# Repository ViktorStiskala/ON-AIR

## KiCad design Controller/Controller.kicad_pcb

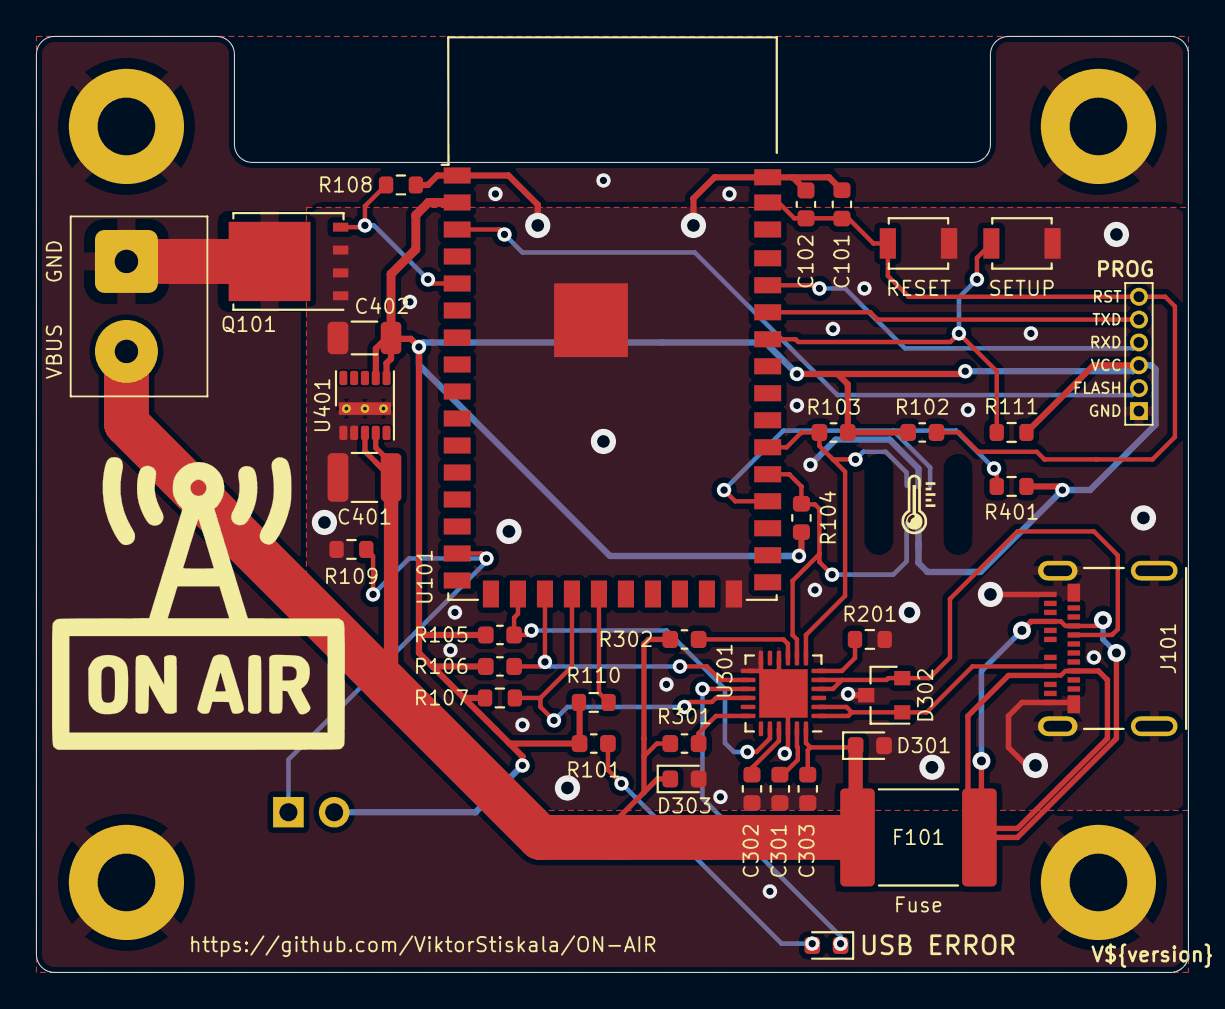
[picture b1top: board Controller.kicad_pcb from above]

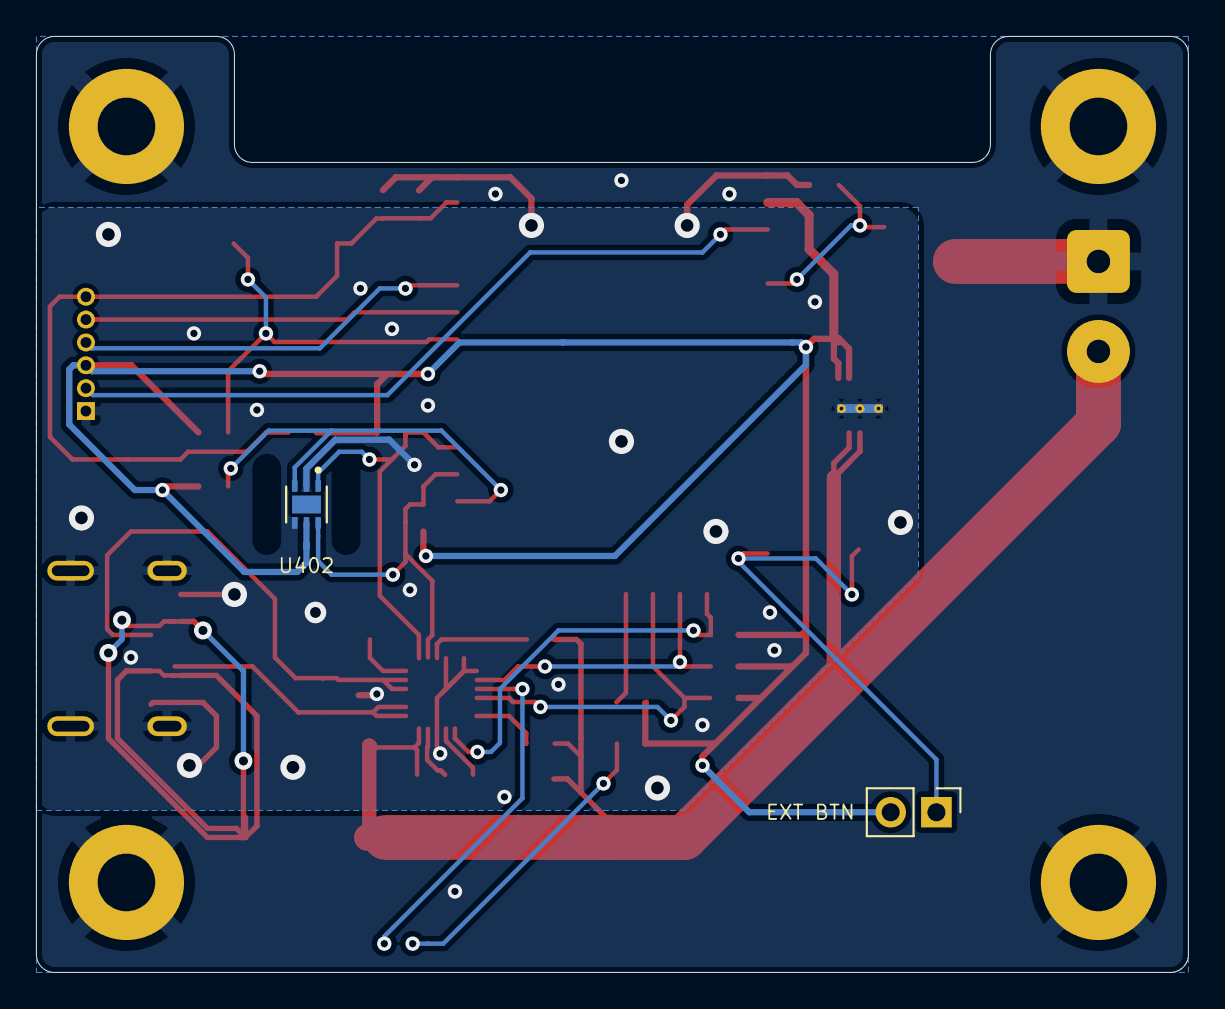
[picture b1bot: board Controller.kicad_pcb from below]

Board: 2 copper layers, 64.0 x 52.0 mm, 44 parts (2 on the bottom side), 28 nets.

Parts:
C101, C301, C302, C303: 1uF; C_0603_1608Metric
C102: 0.1uF; C_0603_1608Metric
C401: 10uF; C_1210_3225Metric
C402: 33uF; C_1206_3216Metric
D101: ERROR; D_0603_1608Metric
D301, D303: ESDA25P35; D_0603_1608Metric
D302: ESDA25W; SOT-23
F101: Polyfuse; Fuse_2920_7451Metric
G101: image; ON_AIR
G102: image; Temperature
H101, H102, H103, H104: Mount; MountingHole_3.2mm_M3_Pad
J101: USB_C_Receptacle; USB_C_Receptacle_Molex_105450-0101
J102: Screw_Terminal_01x02; DG301-5.0-02P-12-18A
P101: ESProg_Mating_Header; ESProg_THT_1.27mm
Q101: BSC0503NSI; TDSON-8-1
R101: 60R; R_0603_1608Metric
R102, R103, R104, R105, R106, R107, R108, R109, R110, R111, R401: 10K; R_0603_1608Metric
R201: 100K; R_0603_1608Metric
R301, R302: 1K; R_0603_1608Metric
SW101: RESET; SW_SPST_B3U-1000P
SW102: SW_EXT; PinHeader_1x02_P2.54mm_Vertical
SW103: SETUP; SW_SPST_B3U-1000P
U101: ESP32-S2-WROVER
U301: STUSB4500QTR; QFN-24-1EP_4x4mm_P0.5mm_EP2.7x2.7mm
U401: LMZM23600V3; Texas_SIL0010A_MicroSiP-10-1EP_3.8x3mm_P0.6mm_EP0.7x2.9mm_T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
U402: TMP117; TMP117_SON65

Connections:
+3V3: C402.2, P101.3 (VCC), R101.2, R102.2, R103.1, R104.1, R105.1, R106.1, R107.1, R110.2, R111.2, R401.1, SW102.2 (B), U101.2 (3V3), U401.6 (VOUT), U401.7 (FB), U402.5 (V+)
/ALERT_TEMP: R401.2, U101.30 (IO36), U402.3 (ALERT)
/CC1: D302.1 (A1), J101.A5 (CC1), U301.1 (CC1DB), U301.2 (CC1)
/CC2: D302.2 (A2), J101.B5 (CC2), U301.4 (CC2), U301.5 (CC2DB)
/ESP_EN: C101.1, C102.1, P101.6 (RST), R102.1, SW101.1, U101.41 (EN)
/ESP_IO0: P101.2 (GPIO0), U101.3 (IO00)
/ESP_RX: P101.4 (RXD), U101.38 (RXD0)
/ESP_TX: P101.5 (TXD), U101.37 (TXD0)
/GND_OUT: H101.1, H102.1, H103.1, H104.1, J102.1, Q101.5 (D)
/GPIO: D101.1 (K), U301.15 (GPIO)
/GP_PWM: Q101.4 (G), R108.2, U101.5 (IO02)
/GP_SETUP: R111.1, SW103.1, U101.36 (IO42)
/IO18: R110.1, U101.21 (IO18)
/POK2: R105.2, U101.18 (IO15), U301.20 (POWER_OK2)
/POK3: R106.2, U101.19 (IO16), U301.14 (POWER_OK3)
/SCL: R103.2, U101.32 (IO38), U301.7 (SCL), U402.1 (SCL)
/SDA: R104.2, U101.31 (IO37), U301.8 (SDA), U402.6 (SDA)
/SW_EXT: R109.2, SW102.1 (A), U101.15 (IO12)
/USB-C PD/RST: R201.2, U301.6 (RESET)
/USB_VIN: F101.2, J101.A4 (VBUS), J101.A9 (VBUS), J101.B4 (VBUS), J101.B9 (VBUS)
/VBUS_EN_SNK: R107.2, U101.20 (IO17), U301.16 (VBUS_EN_SNK)
GND: C101.2, C102.2, C301.2, C302.2, C303.2, C401.1, C402.1, D301.2 (A), D302.3 (common), D303.2 (A), J101.A1 (GND), J101.A12 (GND), J101.B1 (GND), J101.B12 (GND), J101.S1 (SHIELD), P101.1 (GND), Q101.1 (S), Q101.2 (S), Q101.3 (S), R108.1, R109.1, R201.1, SW101.2, SW103.2, U101.1 (GND), U101.26 (GND), U101.42 (GND), U101.43 (GND), U301.10 (GND), U301.12 (ADDR0), U301.13 (ADDR1), U301.22 (VSYS), U301.25 (GND), U401.1 (GND), U401.2 (MODE/SYNC), U401.11 (GND), U402.2 (GND), U402.4 (ADD0)
unnamed: C301.1, U301.23 (VREG_2V7)
unnamed: C302.1, U301.21 (VREG_1V2)
unnamed: D101.2 (A), R101.1
unnamed: R301.1, U301.18 (VBUS_VS_DISCH)
unnamed: R302.2, U301.9 (DISCH)
VBUS: C303.1, C401.2, D301.1 (K), D303.1 (K), F101.1, J102.2, R301.2, R302.1, U301.24 (VDD), U401.3 (VIN), U401.4 (EN)

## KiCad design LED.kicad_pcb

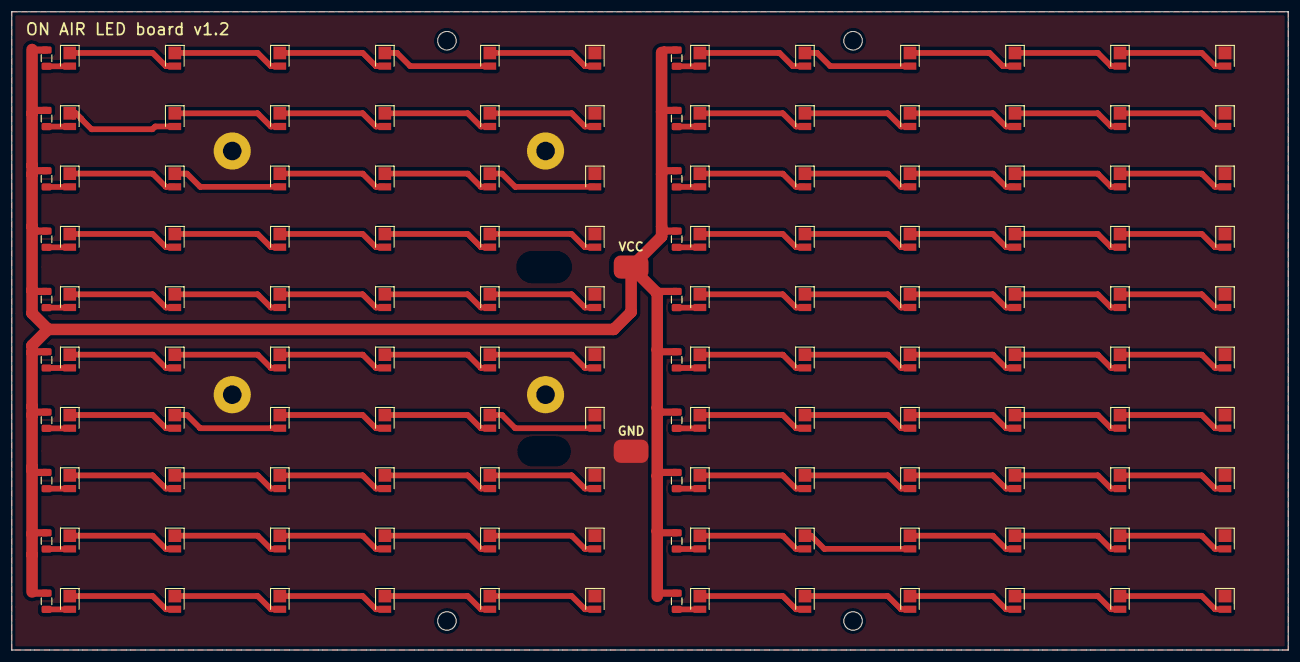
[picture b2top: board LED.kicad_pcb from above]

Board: 2 copper layers, 220.0 x 110.0 mm, 150 parts (0 on the bottom side), 122 nets.

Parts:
D1, D2, D3, D4, D5, D6, D7, D8, D9, D10, D11, D12, D13, D14, D15, D16, D17, D18, D19, D20, D21, D22, D23, D24, D25, D26, D27, D28, D29, D30, D31, D32, D33, D34, D35, D36, D37, D38, D39, D40, D41, D42, D43, D44, D45, D46, D47, D48, D49, D50, D51, D52, D53, D54, D55, D56, D57, D58, D59, D60, D61, D62, D63, D64, D65, D66, D67, D68, D69, D70, D71, D72, D73, D74, D75, D76, D77, D78, D79, D80, D81, D82, D83, D84, D85, D86, D87, D88, D89, D90, D91, D92, D93, D94, D95, D96, D97, D98, D99, D100, D101, D102, D103, D104, D105, D106, D107, D108, D109, D110, D111, D112, D113, D114, D115, D116, D117, D118, D119, D120: LED; LED_PLCC_2835
H1, H2, H3, H4: PCB Mounting Hole; MountingHole_3.2mm_M3_Pad
H5, H6, H7, H8: Mounting Hole; MountingHole_3.2mm_M3
J1, J2: Conn_01x01; PAD_conn_oval
R1, R2, R3, R4, R5, R6, R7, R8, R9, R10, R11, R12, R13, R14, R15, R16, R17, R18, R19, R20: 27R; R_1206_3216Metric

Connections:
+VDC: J2.1, R1.2, R2.2, R3.2, R4.2, R5.2, R6.2, R7.2, R8.2, R9.2, R10.2, R11.2, R12.2, R13.2, R14.2, R15.2, R16.2, R17.2, R18.2, R19.2, R20.2
GND: D6.1, D12.1, D18.1, D24.1, D30.1, D36.1, D42.1, D48.1, D54.1, D60.1, D66.1, D72.1, D78.1, D84.1, D90.1, D96.1, D102.1, D108.1, D114.1, D120.1, H1.1, H2.1, H3.1, H4.1, J1.1
unnamed: D1.1, D2.2
unnamed: D1.2, R1.1
unnamed: D2.1, D3.2
unnamed: D3.1, D4.2
unnamed: D4.1, D5.2
unnamed: D5.1, D6.2
unnamed: D7.1, D8.2
unnamed: D7.2, R2.1
unnamed: D8.1, D9.2
unnamed: D10.1, D11.2
unnamed: D9.1, D10.2
unnamed: D11.1, D12.2
unnamed: D13.1, D14.2
unnamed: D13.2, R3.1
unnamed: D14.1, D15.2
unnamed: D15.1, D16.2
unnamed: D16.1, D17.2
unnamed: D17.1, D18.2
unnamed: D19.1, D20.2
unnamed: D19.2, R4.1
unnamed: D20.1, D21.2
unnamed: D21.1, D22.2
unnamed: D22.1, D23.2
unnamed: D23.1, D24.2
unnamed: D25.1, D26.2
unnamed: D25.2, R5.1
unnamed: D26.1, D27.2
unnamed: D27.1, D28.2
unnamed: D28.1, D29.2
unnamed: D29.1, D30.2
unnamed: D31.1, D32.2
unnamed: D31.2, R6.1
unnamed: D32.1, D33.2
unnamed: D33.1, D34.2
unnamed: D34.1, D35.2
unnamed: D35.1, D36.2
unnamed: D37.1, D38.2
unnamed: D37.2, R7.1
unnamed: D38.1, D39.2
unnamed: D39.1, D40.2
unnamed: D40.1, D41.2
unnamed: D41.1, D42.2
unnamed: D43.1, D44.2
unnamed: D43.2, R8.1
unnamed: D44.1, D45.2
unnamed: D45.1, D46.2
unnamed: D46.1, D47.2
unnamed: D47.1, D48.2
unnamed: D49.1, D50.2
unnamed: D49.2, R9.1
unnamed: D50.1, D51.2
unnamed: D51.1, D52.2
unnamed: D52.1, D53.2
unnamed: D53.1, D54.2
unnamed: D55.1, D56.2
unnamed: D55.2, R10.1
unnamed: D56.1, D57.2
unnamed: D57.1, D58.2
unnamed: D58.1, D59.2
unnamed: D59.1, D60.2
unnamed: D61.1, D62.2
unnamed: D61.2, R11.1
unnamed: D62.1, D63.2
unnamed: D63.1, D64.2
unnamed: D64.1, D65.2
unnamed: D65.1, D66.2
unnamed: D67.1, D68.2
unnamed: D67.2, R12.1
unnamed: D68.1, D69.2
unnamed: D69.1, D70.2
unnamed: D70.1, D71.2
unnamed: D71.1, D72.2
unnamed: D73.1, D74.2
unnamed: D73.2, R13.1
unnamed: D74.1, D75.2
unnamed: D75.1, D76.2
unnamed: D76.1, D77.2
unnamed: D77.1, D78.2
unnamed: D79.1, D80.2
unnamed: D79.2, R14.1
unnamed: D80.1, D81.2
unnamed: D81.1, D82.2
unnamed: D82.1, D83.2
unnamed: D83.1, D84.2
unnamed: D85.1, D86.2
unnamed: D85.2, R15.1
unnamed: D86.1, D87.2
unnamed: D87.1, D88.2
unnamed: D88.1, D89.2
unnamed: D89.1, D90.2
unnamed: D91.1, D92.2
unnamed: D91.2, R16.1
unnamed: D92.1, D93.2
unnamed: D93.1, D94.2
unnamed: D94.1, D95.2
unnamed: D95.1, D96.2
unnamed: D97.1, D98.2
unnamed: D97.2, R17.1
unnamed: D98.1, D99.2
unnamed: D100.1, D101.2
unnamed: D99.1, D100.2
unnamed: D101.1, D102.2
unnamed: D103.1, D104.2
unnamed: D103.2, R18.1
unnamed: D104.1, D105.2
unnamed: D105.1, D106.2
unnamed: D106.1, D107.2
unnamed: D107.1, D108.2
unnamed: D109.1, D110.2
unnamed: D109.2, R19.1
unnamed: D110.1, D111.2
unnamed: D111.1, D112.2
unnamed: D112.1, D113.2
unnamed: D113.1, D114.2
unnamed: D115.1, D116.2
unnamed: D115.2, R20.1
unnamed: D116.1, D117.2
unnamed: D117.1, D118.2
unnamed: D118.1, D119.2
unnamed: D119.1, D120.2

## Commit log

2020-10-03 Replaced ESP8266 with ESP32-S2-WROOM
2020-10-16 V1.3
